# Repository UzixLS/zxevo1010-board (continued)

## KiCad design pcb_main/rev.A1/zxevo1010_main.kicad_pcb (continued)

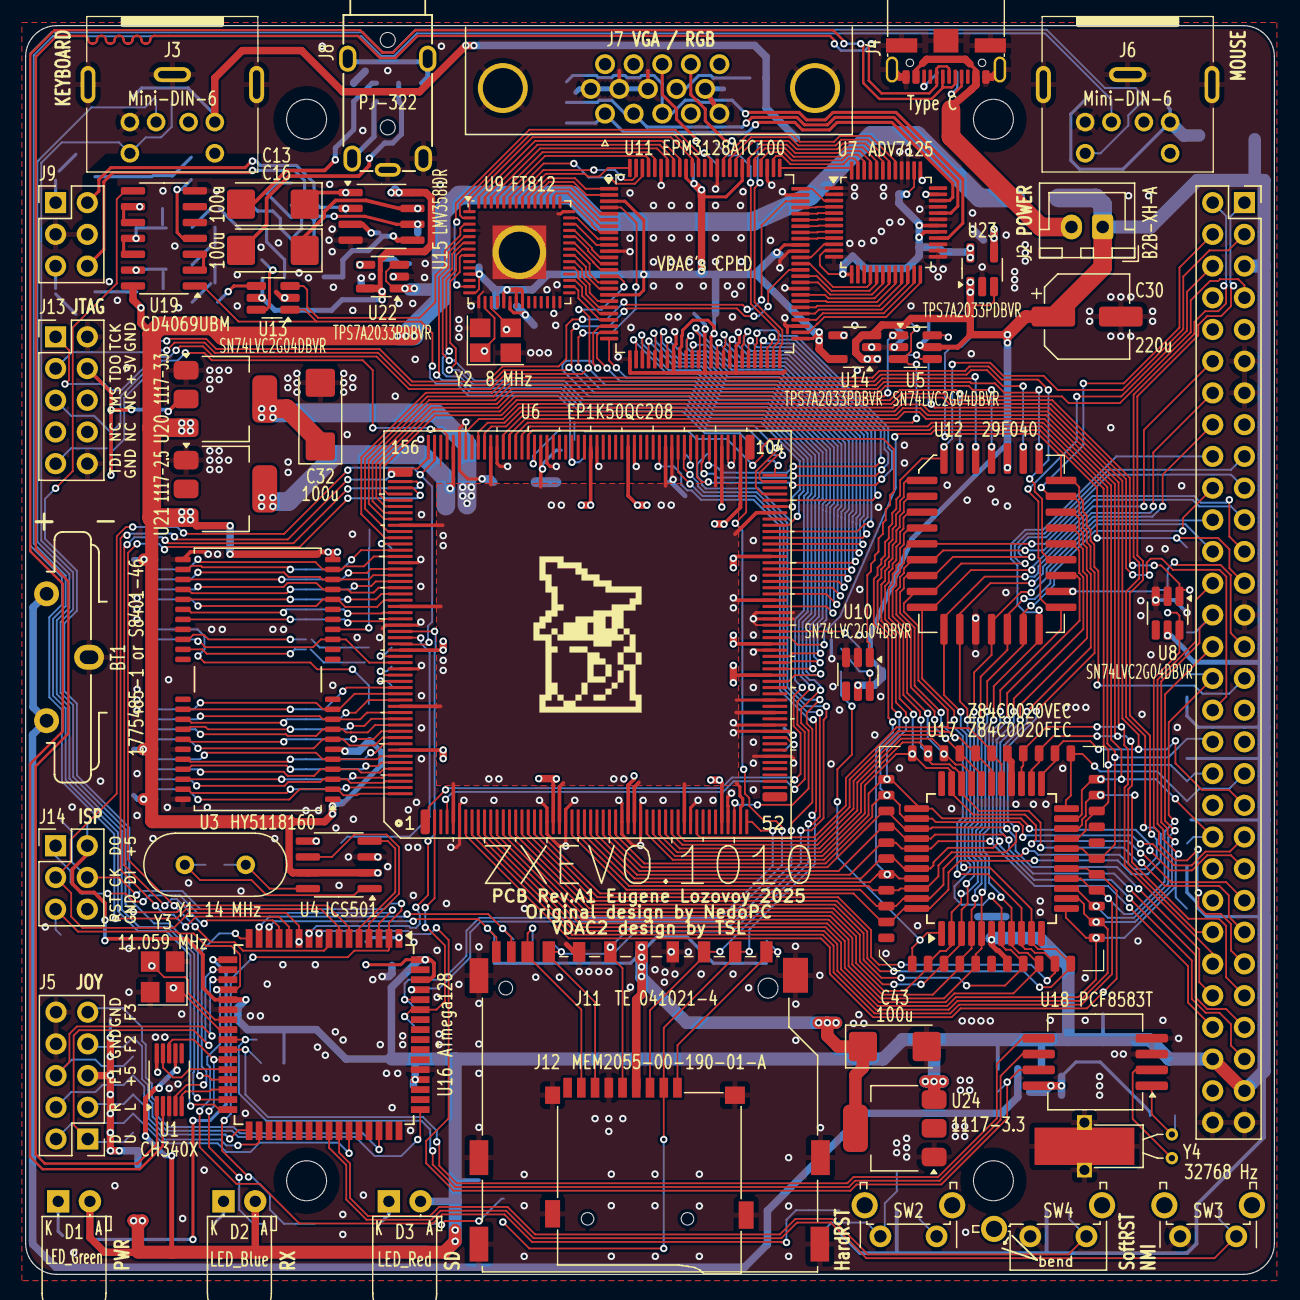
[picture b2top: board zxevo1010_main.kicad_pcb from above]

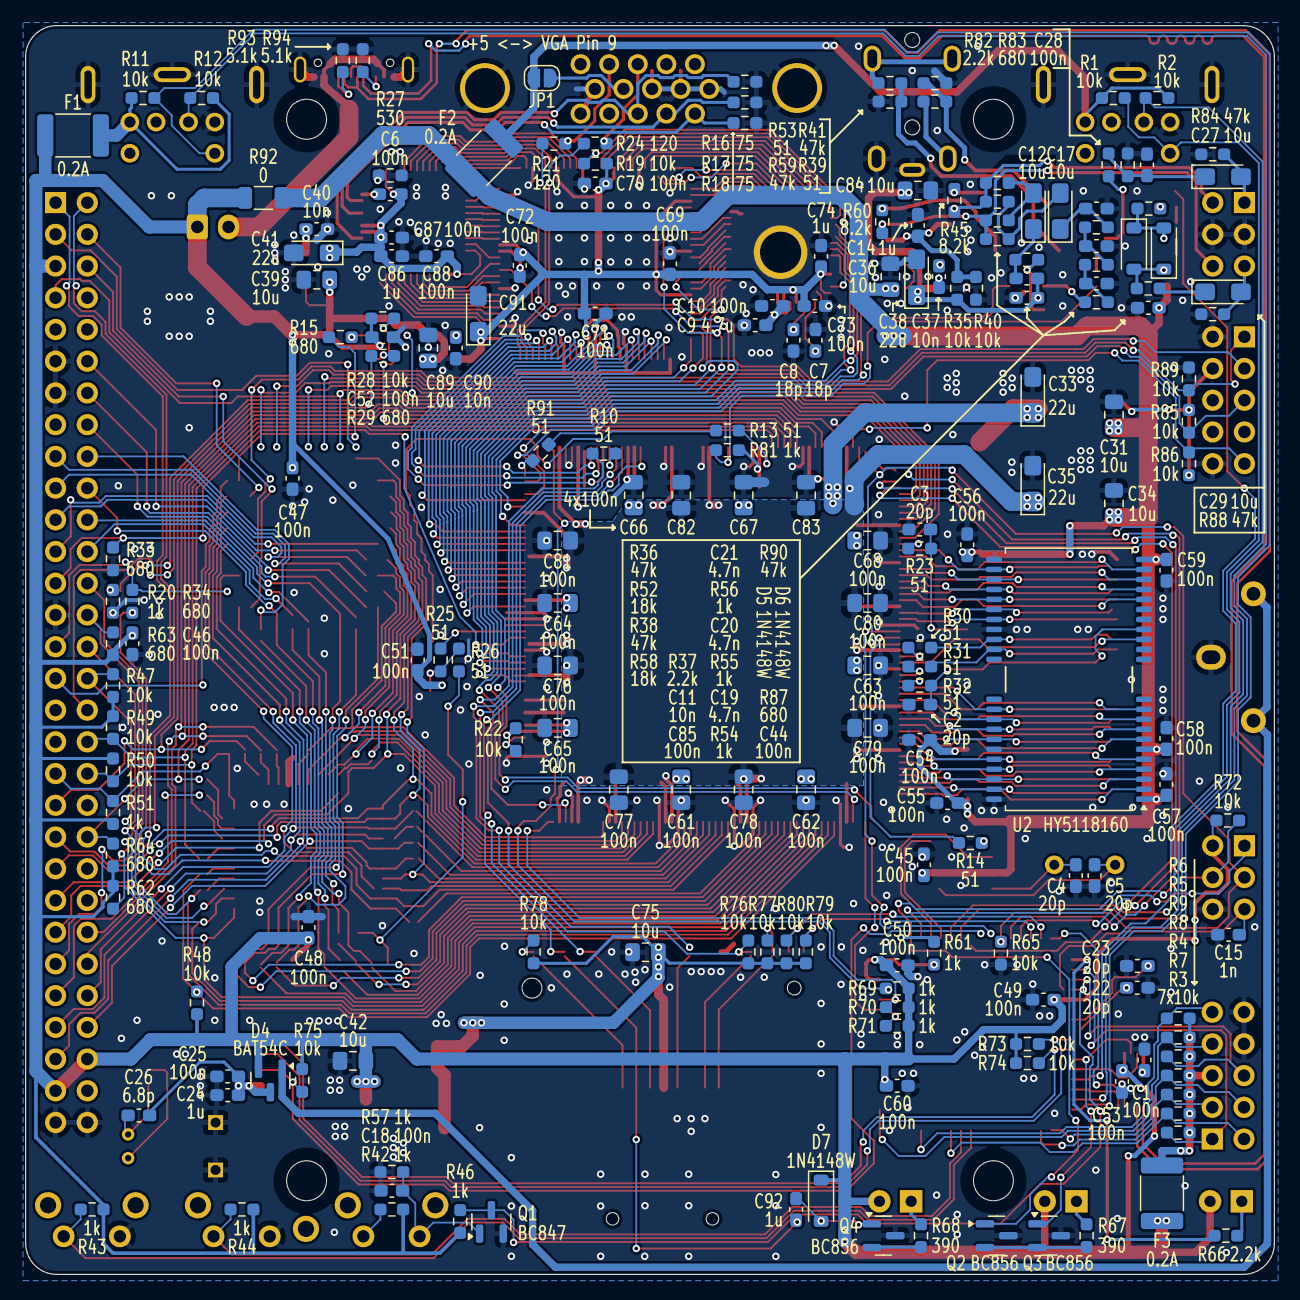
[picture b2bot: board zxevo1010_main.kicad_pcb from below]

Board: 2 copper layers, 100.0 x 100.0 mm, 252 parts (194 on the bottom side), 302 nets.

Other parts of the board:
LOGO1: graphic; black-mage-12.5x8.6-r

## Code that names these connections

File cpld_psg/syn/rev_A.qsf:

# -------------------------------------------------------------------------- #
#
# Copyright (C) 1991-2013 Altera Corporation
# Your use of Altera Corporation's design tools, logic functions 
# and other software and tools, and its AMPP partner logic 
# functions, and any output files from any of the foregoing 
# (including device programming or simulation files), and any 
# associated documentation or information are expressly subject 
# to the terms and conditions of the Altera Program License 
# Subscription Agreement, Altera MegaCore Function License 
# Agreement, or other applicable license agreement, including, 
# without limitation, that your use is for the sole purpose of 
# programming logic devices manufactured by Altera and sold by 
# Altera or its authorized distributors.  Please refer to the 
# applicable agreement for further details.
#
# -------------------------------------------------------------------------- #
#
# Quartus II 64-Bit
# Version 13.0.1 Build 232 06/12/2013 Service Pack 1 SJ Full Version
# Date created = 12:04:27  October 04, 2020
#
# -------------------------------------------------------------------------- #
#
# Notes:
#
# 1) The default values for assignments are stored in the file:
#		zxevo1010_psg_assignment_defaults.qdf
#    If this file doesn't exist, see file:
#		assignment_defaults.qdf
#
# 2) Altera recommends that you do not modify this file. This
#    file is updated automatically by the Quartus II software
#    and any changes you make may be lost or overwritten.
#
# -------------------------------------------------------------------------- #


set_global_assignment -name FAMILY MAX3000A
set_global_assignment -name DEVICE "EPM3128ATC100-10"
set_global_assignment -name TOP_LEVEL_ENTITY zxevo1010_psg
set_global_assignment -name ORIGINAL_QUARTUS_VERSION "13.0 SP1"
set_global_assignment -name PROJECT_CREATION_TIME_DATE "12:04:27  OCTOBER 04, 2020"
set_global_assignment -name LAST_QUARTUS_VERSION "13.0 SP1"
set_global_assignment -name PROJECT_OUTPUT_DIRECTORY output
set_global_assignment -name DEVICE_FILTER_PIN_COUNT 100
set_global_assignment -name ERROR_CHECK_FREQUENCY_DIVISOR "-1"
set_global_assignment -name SDC_FILE clocks.sdc
set_global_assignment -name VHDL_INPUT_VERSION VHDL_2008
set_global_assignment -name VHDL_SHOW_LMF_MAPPING_MESSAGES OFF
set_global_assignment -name VERILOG_INPUT_VERSION SYSTEMVERILOG_2005
set_global_assignment -name VERILOG_SHOW_LMF_MAPPING_MESSAGES OFF
set_global_assignment -name MAX7000_DEVICE_IO_STANDARD "3.3-V LVTTL"
set_global_assignment -name SAVE_DISK_SPACE OFF
set_global_assignment -name TIMEQUEST_MULTICORNER_ANALYSIS OFF
set_global_assignment -name SYNTH_TIMING_DRIVEN_SYNTHESIS OFF
set_global_assignment -name MAX7000_OPTIMIZATION_TECHNIQUE SPEED
set_global_assignment -name PRE_MAPPING_RESYNTHESIS OFF
set_global_assignment -name OPTIMIZE_HOLD_TIMING OFF
set_global_assignment -name OPTIMIZE_MULTI_CORNER_TIMING ON
set_global_assignment -name FITTER_EFFORT "STANDARD FIT"
set_global_assignment -name RESERVE_ALL_UNUSED_PINS_NO_OUTPUT_GND "AS INPUT TRI-STATED"

set_location_assignment PIN_6 -to ymd[4]
set_location_assignment PIN_8 -to ymd[5]
set_location_assignment PIN_9 -to ymd[6]
set_location_assignment PIN_10 -to ymd[7]
set_location_assignment PIN_12 -to ymrst_n
set_location_assignment PIN_13 -to ymcs0_n
set_location_assignment PIN_14 -to ymcs1_n
set_location_assignment PIN_16 -to ymwr_n
set_location_assignment PIN_17 -to ymrd_n
set_location_assignment PIN_19 -to yma[0]
set_location_assignment PIN_20 -to yma[1]
set_location_assignment PIN_21 -to ymck
set_location_assignment PIN_23 -to sd_r_1bit
set_location_assignment PIN_25 -to sd_l_1bit
set_location_assignment PIN_30 -to zxd[7]
set_location_assignment PIN_31 -to zxd[0]
set_location_assignment PIN_32 -to zxd[1]
set_location_assignment PIN_35 -to zxd[2]
set_location_assignment PIN_36 -to zxd[6]
set_location_assignment PIN_37 -to zxd[5]
set_location_assignment PIN_40 -to zxd[3]
set_location_assignment PIN_41 -to zxd[4]
set_location_assignment PIN_42 -to zxm1_n
set_location_assignment PIN_44 -to zxal[4]
set_location_assignment PIN_45 -to zxal[5]
set_location_assignment PIN_46 -to zxal[6]
set_location_assignment PIN_47 -to zxal[7]
set_location_assignment PIN_48 -to zxwr_n
set_location_assignment PIN_52 -to zxrd_n
set_location_assignment PIN_54 -to zxmreq_n
set_location_assignment PIN_56 -to zxal[3]
set_location_assignment PIN_57 -to zxal[2]
set_location_assignment PIN_58 -to zxal[1]
set_location_assignment PIN_60 -to zxal[0]
set_location_assignment PIN_61 -to zxah[13]
set_location_assignment PIN_63 -to zxah[14]
set_location_assignment PIN_64 -to zxah[15]
set_location_assignment PIN_89 -to zxres_n
set_location_assignment PIN_90 -to clk
set_location_assignment PIN_92 -to midi_clk
set_location_assignment PIN_93 -to midi_rst_n
set_location_assignment PIN_94 -to midi_sense
set_location_assignment PIN_96 -to midi_data
set_location_assignment PIN_97 -to ymd[3]
set_location_assignment PIN_98 -to ymd[0]
set_location_assignment PIN_99 -to ymd[1]
set_location_assignment PIN_100 -to ymd[2]

set_global_assignment -name VERILOG_FILE ../rtl/top.v

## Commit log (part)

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2024-08-21 init
2024-08-21 wip pcbs rev.A
2024-08-31 wip pcb rev.A
2024-10-01 wip pcb rev.A. Main board almost done
2024-10-29 wip pcb rev.A (almost done)
2025-03-27 pcb rev.A final versions
2025-03-27 add firmwares
2025-04-21 add psg cpld firmware
2025-04-26 update neogs rom to the latest version from svn
2025-04-26 add workarround to prevent baseconf crashes
    In the current state BaseConf crashing when entering into 48k basic from main ERS menu. This may or may not happens depending of Virtual Drive, Memory Lock, CPU frequency, Emu tape load settings. Cra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
2025-04-28 add readme; add images
2025-04-28 cpld_psg: fix ymf288 bus timings
2025-04-29 add rev.A1 for all pcbs + release
2025-05-01 minor update readme + images
2026-06-17 remove raw=true from README links
